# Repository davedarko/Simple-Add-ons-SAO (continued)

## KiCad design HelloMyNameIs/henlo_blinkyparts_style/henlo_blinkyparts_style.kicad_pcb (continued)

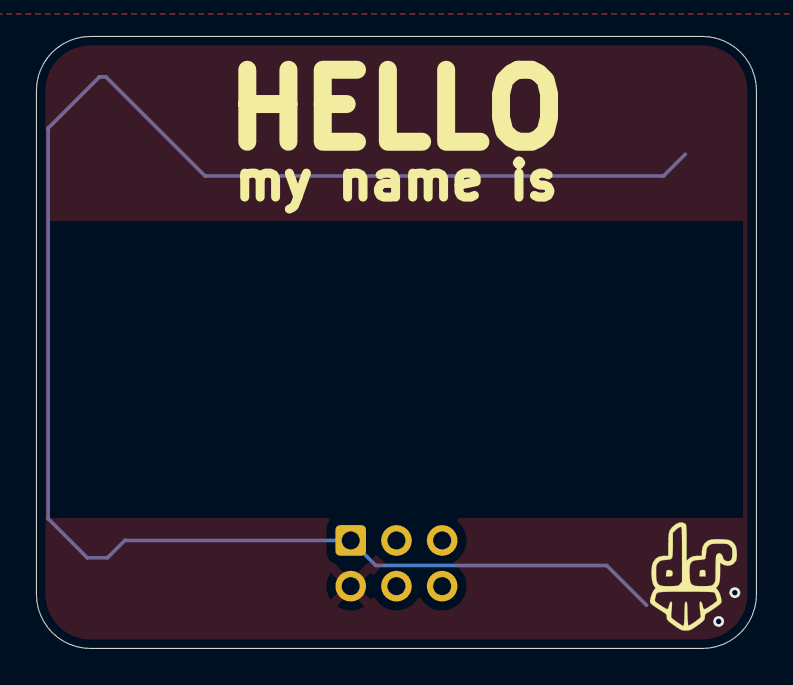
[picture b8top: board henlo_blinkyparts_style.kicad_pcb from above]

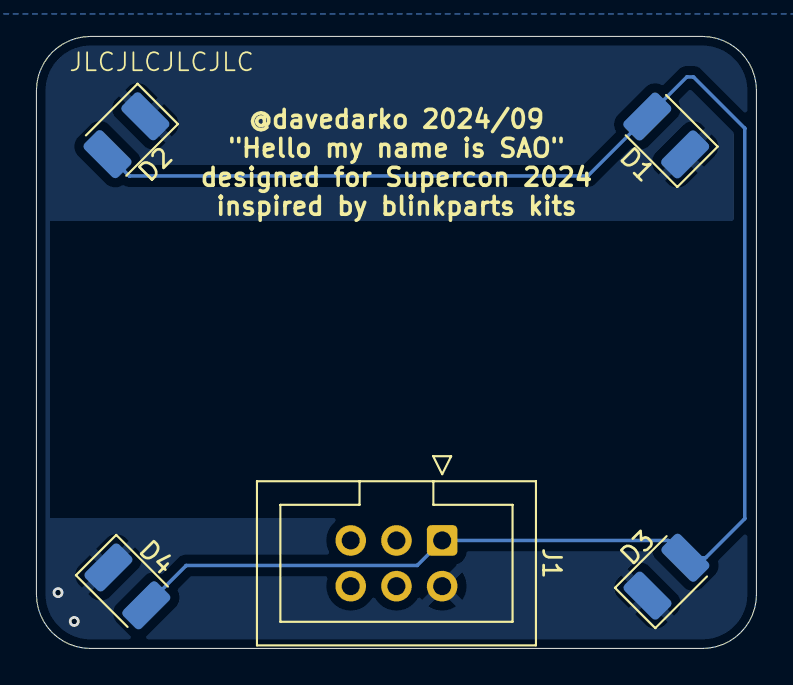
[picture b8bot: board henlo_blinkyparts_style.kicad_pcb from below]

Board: 2 copper layers, 40.0 x 34.0 mm, 6 parts (5 on the bottom side), 2 nets.

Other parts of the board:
Ref**: Val**; davedarko_logo_silk_outline

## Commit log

2022-10-18 Update .gitignore
    added eagle bits
2022-10-18 remove mac stuff
2022-10-18 removed backups
2022-10-18 covid19 test sao
2022-10-18 library stick for SAOs
2022-10-18 vendettaSAO
2022-10-18 Mr Robot Badge with Code
2022-10-19 added phengicorn SAO badge
    found it on the penghicorn repo
2022-10-21 wrong file name
2022-11-14 moved labels, gerber version 3 for HiP.berlin
2023-11-15 added more SAO
2024-09-05 added more SAOs and converted to Kicad8
2024-09-05 kitt SAO
2024-10-05 added 2 more and updated solo
2024-10-11 updated production HelloMyNameIs
2024-11-03 slides
2026-05-19 Added more designs and updates
2026-05-21 added LECCO
